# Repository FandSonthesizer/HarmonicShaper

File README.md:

# HarmonicShaper

This is a project where we take an audio-input signal, filter a rectangular wave from it and use that to create harmonics below or above the input signal.

Features:
- can be used directly with electric guitar output or a synthesizer output.
- 4 harmonic waves can be generated
- selectable waveform: SIN, TRI, RMP, SAW and Square
- Clean and harmonic blend mixer
- harmonics adjustable from 7 undertones to 7 overtones 

It is based on our Essential Shield.

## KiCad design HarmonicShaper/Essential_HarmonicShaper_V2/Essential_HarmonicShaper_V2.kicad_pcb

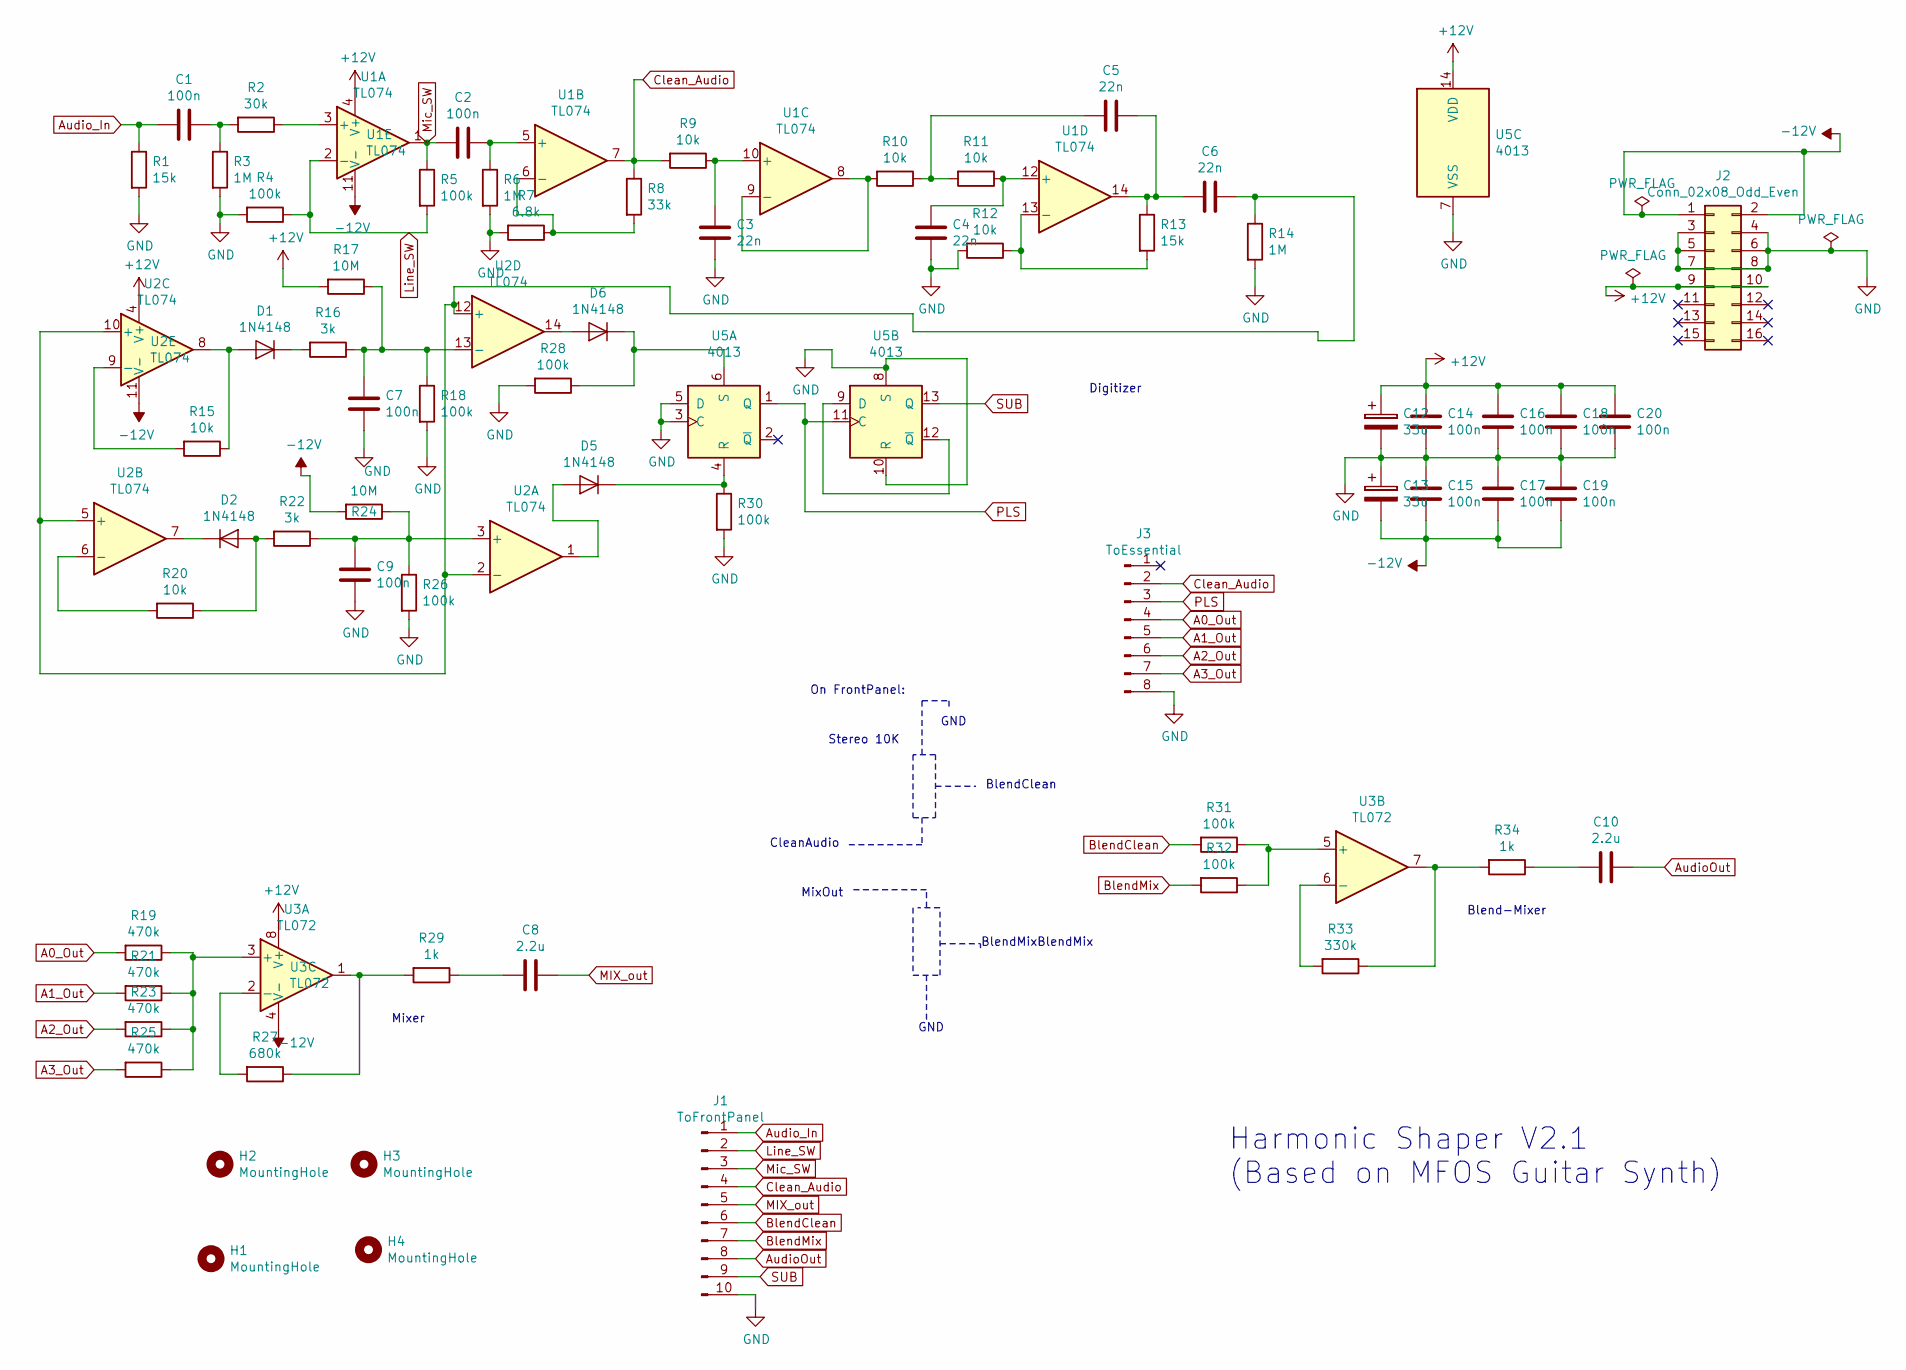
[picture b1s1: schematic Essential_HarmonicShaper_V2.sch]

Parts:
C1, C2, C7, C9, C14, C15, C16, C17, C18, C19, C20: 100n; Kondensator_Keramik
C3, C4, C5, C6: 22n; Kondensator_Keramik
C8, C10: 2.2u; Kondensator_Keramik
C12, C13: 33u; Elko_D6.3mm_P2.50mm
D1, D2, D5, D6: 1N4148; Diode_Horizontal
H1, H2, H3, H4: MountingHole; MountHole
J1: ToFrontPanel; PinHeader_1x10_P2.54mm_Vertical
J2: Conn_02x08_Odd_Even; PinHeader_2x08_P2.54mm_Vertical
J3: ToEssential; PinHeader_1x08_P2.54mm_Vertical
R1, R13: 15k; Widerstand_liegend
R2: 30k; Widerstand_liegend
R3, R6, R14: 1M; Widerstand_liegend
R4, R5, R18, R26, R28, R30, R31, R32: 100k; Widerstand_liegend
R7: 6.8k; Widerstand_liegend
R8: 33k; Widerstand_liegend
R9, R10, R11, R12, R15, R20: 10k; Widerstand_liegend
R16, R22: 3k; Widerstand_liegend
R17, R24: 10M; Widerstand_liegend
R19, R21, R23, R25: 470k; Widerstand_liegend
R27: 680k; Widerstand_liegend
R29, R34: 1k; Widerstand_liegend
R33: 330k; Widerstand_liegend
U1, U2: TL074; DIP-14_W7.62mm_LongPads
U3: TL072; DIP-8_W7.62mm_Socket_LongPads
U5: 4013; DIP-14_W7.62mm_LongPads

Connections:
+12V: C12.1, C14.1, C16.1, C18.1, C20.1, J2.9, J2.10, R17.2, U1.4 (V+), U2.4 (V+), U3.8 (V+), U5.14 (VDD)
-12V: C13.2, C15.2, C17.2, C19.2, J2.1, J2.2, R24.2, U1.11 (V-), U2.11 (V-), U3.4 (V-)
A0_Out: J3.4, R19.2
A1_Out: J3.5, R21.2
A2_Out: J3.6, R23.2
A3_Out: J3.7, R25.2
AudioOut: C10.2, J1.8
Audio_In: C1.1, J1.1, R1.1
BlendClean: J1.6, R31.2
BlendMix: J1.7, R32.2
Clean_Audio: J1.4, J3.2, R8.1, R9.2, U1.7
GND: C3.2, C4.2, C7.2, C9.2, C12.2, C13.1, C14.2, C15.1, C16.2, C17.1, C18.2, C19.1, C20.2, J1.10, J2.3, J2.4, J2.5, J2.6, J2.7, J2.8, J3.8, R1.2, R3.2, R4.2, R6.2, R7.2, R12.2, R14.2, R18.2, R26.2, R28.2, R30.2, U5.3 (C), U5.5 (D), U5.7 (VSS), U5.8 (S), U5.10 (R)
Line_SW: J1.2, R4.1, R5.2, U1.2 (-)
MIX_out: C8.2, J1.5
Mic_SW: C2.1, J1.3, R5.1, U1.1
unnamed: C1.2, R2.2, R3.1
unnamed: C2.2, R6.1, U1.5 (+)
unnamed: C3.1, R9.1, U1.10 (+)
unnamed: C4.1, R11.1, U1.12 (+)
unnamed: C5.1, C6.2, R13.1, U1.14
unnamed: C5.2, R10.1, R11.2
unnamed: C6.1, R14.1, U2.2 (-), U2.5 (+), U2.10 (+), U2.12 (+)
unnamed: C7.1, R16.1, R17.1, R18.1, U2.13 (-)
unnamed: C8.1, R29.1
unnamed: C9.1, R22.1, R24.1, R26.1, U2.3 (+)
unnamed: C10.1, R34.1
unnamed: D1.1 (K), R16.2
unnamed: D1.2 (A), R15.1, U2.8
unnamed: D2.1 (K), U2.7
unnamed: D2.2 (A), R20.1, R22.2
unnamed: D5.1 (K), R30.1, U5.4 (R)
unnamed: D5.2 (A), U2.1
unnamed: D6.1 (K), R28.1, U5.6 (S)
unnamed: D6.2 (A), U2.14
unnamed: R2.1, U1.3 (+)
unnamed: R7.1, R8.2, U1.6 (-)
unnamed: R10.2, U1.8, U1.9 (-)
unnamed: R12.1, R13.2, U1.13 (-)
unnamed: R15.2, U2.9 (-)
unnamed: R19.1, R21.1, R23.1, R25.1, U3.3 (+)
unnamed: R20.2, U2.6 (-)
unnamed: R27.1, R29.2, U3.1
unnamed: R27.2, U3.2 (-)
unnamed: R31.1, R32.1, U3.5 (+)
unnamed: R33.1, R34.2, U3.7
unnamed: R33.2, U3.6 (-)
unnamed: U5.9 (D), U5.12 (~Q)
PLS: J3.3, U5.1 (Q), U5.11 (C)
SUB: J1.9, U5.13 (Q)

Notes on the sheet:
Harmonic Shaper V2.1 (Based on MFOS Guitar Synth)
Mixer
Digitizer
Blend-Mixer
Stereo 10K
GND
MixOut
CleanAudio
On FrontPanel:
BlendClean
BlendMixBlendMix

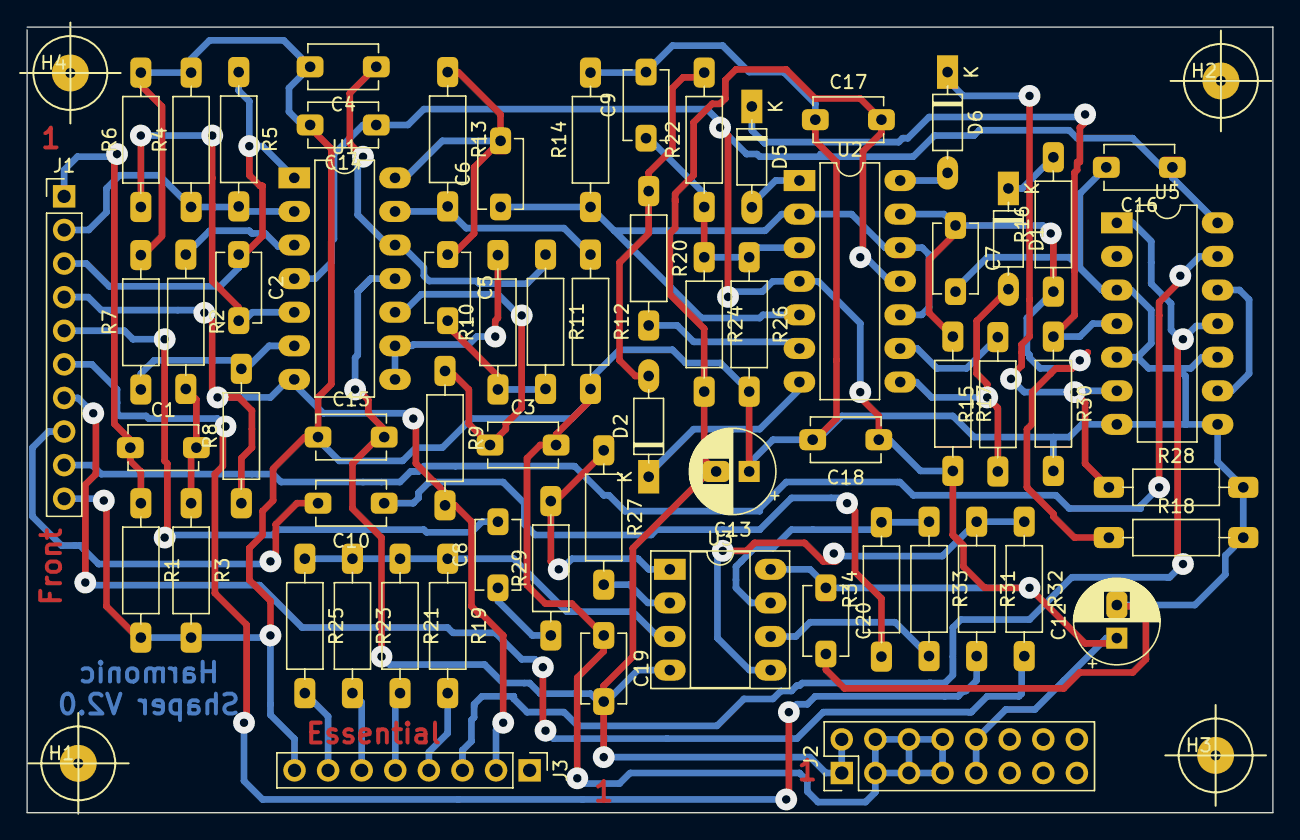
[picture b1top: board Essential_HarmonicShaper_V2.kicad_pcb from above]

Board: 2 copper layers, 94.2 x 59.4 mm, 68 parts (0 on the bottom side), 49 nets.
